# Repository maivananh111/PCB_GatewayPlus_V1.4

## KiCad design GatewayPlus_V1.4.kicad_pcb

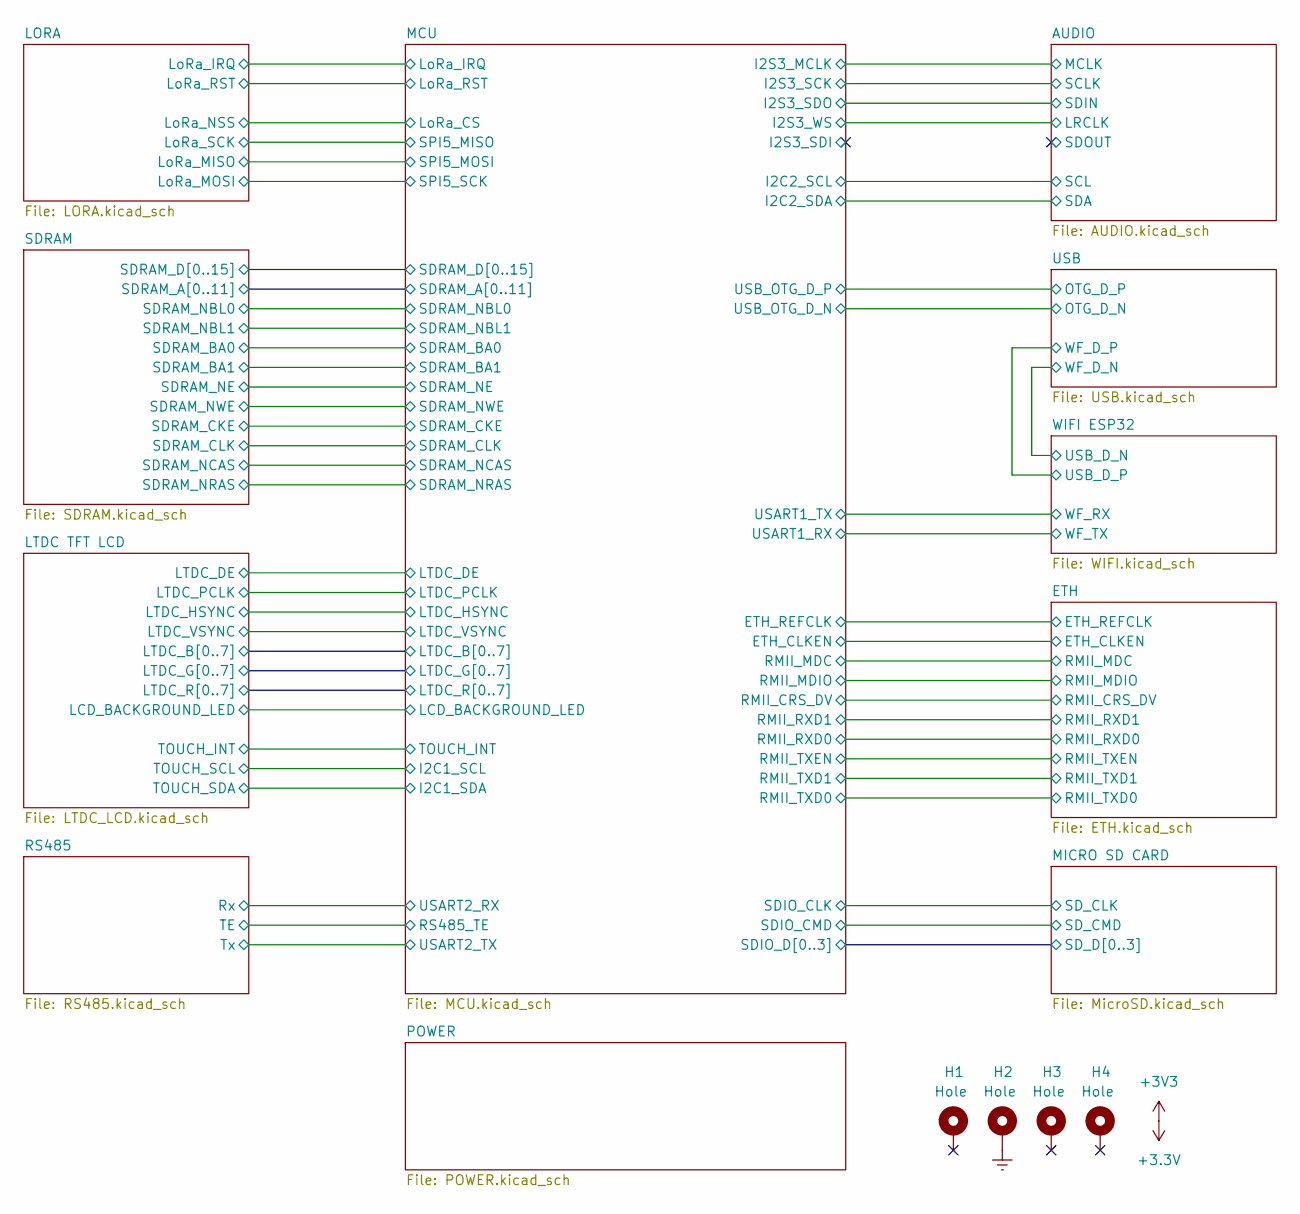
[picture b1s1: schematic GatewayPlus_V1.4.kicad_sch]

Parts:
H1, H2, H3, H4: Hole; MountingHole_3.2mm_M3_Pad_Via

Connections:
Earth: H2.1; also elsewhere on the board

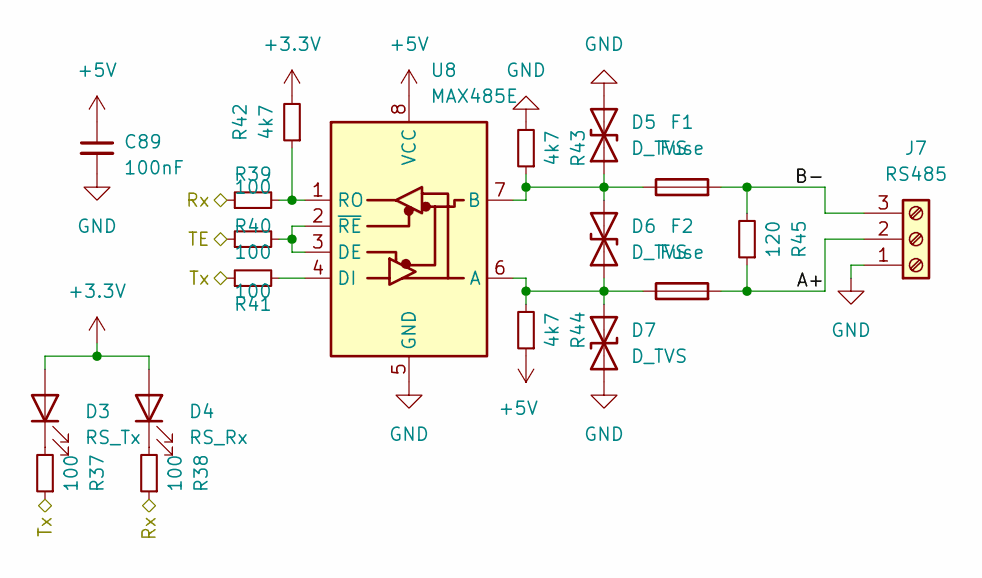
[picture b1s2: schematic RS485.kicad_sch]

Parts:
C89: 100nF; C_0603
D3: RS_Tx; LED_0603
D4: RS_Rx; LED_0603
D5, D6, D7: D_TVS; D_SMA
F1, F2: Fuse; F_1206
J7: RS485; TerminalBlock_Phoenix_MKDS-1,5-3-5.08_1x03_P5.08mm_Horizont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
R37, R38, R39, R40, R41: 100; R_0603
R42, R43, R44: 4k7; R_0603
R45: 120; R_0805
U8: MAX485E; SOIC-8

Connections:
/MCU/RS485_TE: R40.1; also elsewhere on the board
/MCU/USART2_RX: R38.1, R39.1; also elsewhere on the board
/MCU/USART2_TX: R37.1, R41.1; also elsewhere on the board
/RS485/A+: F2.2, J7.2, R45.1
/RS485/B-: F1.2, J7.3, R45.2
GND: C89.2, D5.2 (A2), D7.2 (A2), J7.1, R43.2, U8.5 (GND); also elsewhere on the board
unnamed: D3.1 (K), R37.2
unnamed: D4.1 (K), R38.2
unnamed: D5.1 (A1), D6.2 (A2), F1.1, R43.1, U8.7 (B)
unnamed: D6.1 (A1), D7.1 (A1), F2.1, R44.2, U8.6 (A)
unnamed: R40.2, U8.2 (~RE), U8.3 (DE)
unnamed: R41.2, U8.4 (DI)
unnamed: R39.2, R42.1, U8.1 (RO)

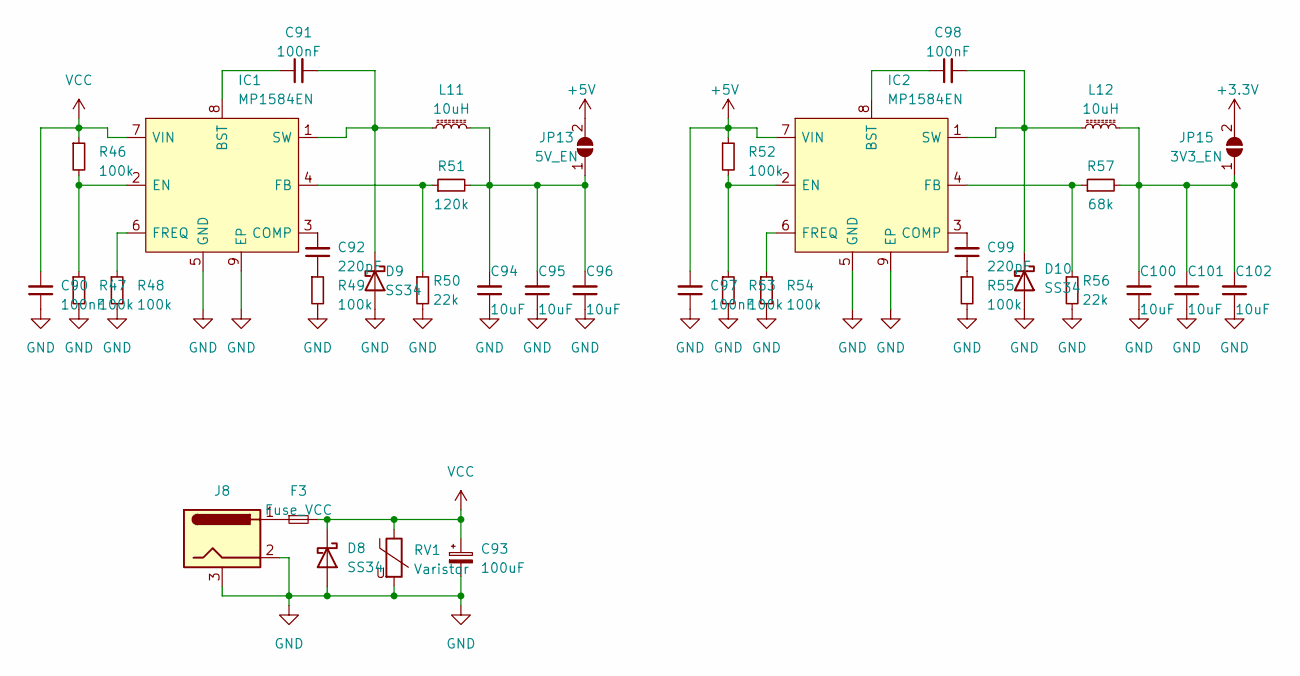
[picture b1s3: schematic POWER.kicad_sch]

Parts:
C90, C91, C97, C98: 100nF; C_0603
C92, C99: 220pF; C_0603
C93: 100uF; CP_Elec_6.3x5.4
C94, C95, C96, C100, C101, C102: 10uF; C_1210
D8, D9, D10: SS34; D_SMA
F3: Fuse_VCC; F_1206
IC1, IC2: MP1584EN; SOIC-8_PAD_VIAS
J8: Conn_Jack-DC; DC_PowerJack_5mm_THT
JP13: 5V_EN; SolderJumper-2_P1.3mm_Open_RoundedPad1.0x1.5mm
JP15: 3V3_EN; SolderJumper-2_P1.3mm_Open_RoundedPad1.0x1.5mm
L11, L12: 10uH; L_Abracon_ASPI-0630LR
R46, R47, R48, R49, R52, R53, R54, R55: 100k; R_0603
R50, R56: 22k; R_0603
R51: 120k; R_0603
R57: 68k; R_0603
RV1: Varistor; RV_Disc_D9mm_W3.3mm_P5mm

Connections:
GND: C90.1, C93.2, C94.1, C95.1, C96.1, C97.1, C100.1, C101.1, C102.1, D8.2 (A), D9.2 (A), D10.2 (A), IC1.5 (GND), IC1.9 (EP), IC2.5 (GND), IC2.9 (EP), J8.2, J8.3, R47.2, R48.2, R49.2, R50.2, R53.2, R54.2, R55.2, R56.2, RV1.2; also elsewhere on the board
unnamed: C92.1, R49.1
unnamed: C99.1, R55.1
unnamed: C91.2, D9.1 (K), IC1.1 (SW), L11.1
unnamed: C98.2, D10.1 (K), IC2.1 (SW), L12.1
unnamed: F3.1, J8.1
unnamed: C91.1, IC1.8 (BST)
unnamed: C92.2, IC1.3 (COMP)
unnamed: IC1.2 (EN), R46.2, R47.1
unnamed: IC1.4 (FB), R50.1, R51.1
unnamed: IC1.6 (FREQ), R48.1
unnamed: C98.1, IC2.8 (BST)
unnamed: C99.2, IC2.3 (COMP)
unnamed: IC2.2 (EN), R52.2, R53.1
unnamed: IC2.4 (FB), R56.1, R57.1
unnamed: IC2.6 (FREQ), R54.1
unnamed: C94.2, C95.2, C96.2, JP13.1 (A), L11.2, R51.2
unnamed: C100.2, C101.2, C102.2, JP15.1 (A), L12.2, R57.2
VCC: C90.2, C93.1, D8.1 (K), F3.2, IC1.7 (VIN), R46.1, RV1.1

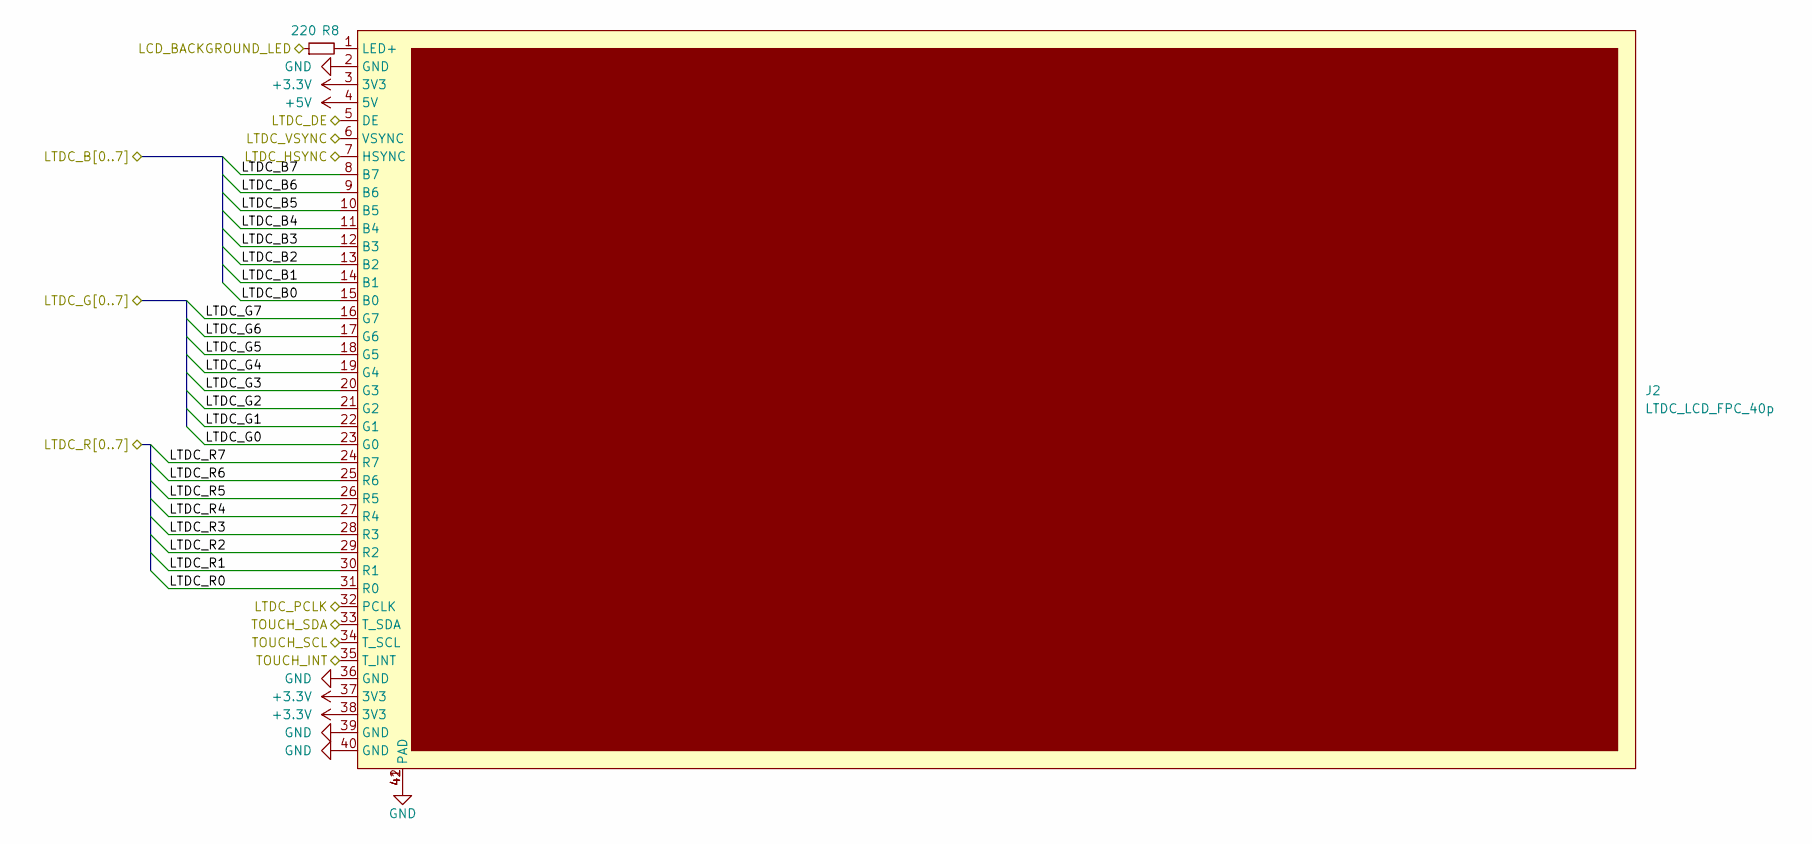
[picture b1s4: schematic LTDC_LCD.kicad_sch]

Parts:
J2: LTDC_LCD_FPC_40p; FPC_40p_Vertical
R8: 220; R_0603

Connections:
/LTDC TFT LCD/LCD_BACKGROUND_LED: R8.1; also elsewhere on the board
/LTDC TFT LCD/LTDC_B0: J2.15 (B0); also elsewhere on the board
/LTDC TFT LCD/LTDC_B1: J2.14 (B1); also elsewhere on the board
/LTDC TFT LCD/LTDC_B2: J2.13 (B2); also elsewhere on the board
/LTDC TFT LCD/LTDC_B3: J2.12 (B3); also elsewhere on the board
/LTDC TFT LCD/LTDC_B4: J2.11 (B4); also elsewhere on the board
/LTDC TFT LCD/LTDC_B5: J2.10 (B5); also elsewhere on the board
/LTDC TFT LCD/LTDC_B6: J2.9 (B6); also elsewhere on the board
/LTDC TFT LCD/LTDC_B7: J2.8 (B7); also elsewhere on the board
/LTDC TFT LCD/LTDC_DE: J2.5 (DE); also elsewhere on the board
/LTDC TFT LCD/LTDC_G0: J2.23 (G0); also elsewhere on the board
/LTDC TFT LCD/LTDC_G1: J2.22 (G1); also elsewhere on the board
/LTDC TFT LCD/LTDC_G2: J2.21 (G2); also elsewhere on the board
/LTDC TFT LCD/LTDC_G3: J2.20 (G3); also elsewhere on the board
/LTDC TFT LCD/LTDC_G4: J2.19 (G4); also elsewhere on the board
/LTDC TFT LCD/LTDC_G5: J2.18 (G5); also elsewhere on the board
/LTDC TFT LCD/LTDC_G6: J2.17 (G6); also elsewhere on the board
/LTDC TFT LCD/LTDC_G7: J2.16 (G7); also elsewhere on the board
/LTDC TFT LCD/LTDC_HSYNC: J2.7 (HSYNC); also elsewhere on the board
/LTDC TFT LCD/LTDC_PCLK: J2.32 (PCLK); also elsewhere on the board
/LTDC TFT LCD/LTDC_R0: J2.31 (R0); also elsewhere on the board
/LTDC TFT LCD/LTDC_R1: J2.30 (R1); also elsewhere on the board
/LTDC TFT LCD/LTDC_R2: J2.29 (R2); also elsewhere on the board
/LTDC TFT LCD/LTDC_R3: J2.28 (R3); also elsewhere on the board
/LTDC TFT LCD/LTDC_R4: J2.27 (R4); also elsewhere on the board
/LTDC TFT LCD/LTDC_R5: J2.26 (R5); also elsewhere on the board
/LTDC TFT LCD/LTDC_R6: J2.25 (R6); also elsewhere on the board
/LTDC TFT LCD/LTDC_R7: J2.24 (R7); also elsewhere on the board
/LTDC TFT LCD/LTDC_VSYNC: J2.6 (VSYNC); also elsewhere on the board
/LTDC TFT LCD/TOUCH_INT: J2.35 (T_INT); also elsewhere on the board
/LTDC TFT LCD/TOUCH_SCL: J2.34 (T_SCL); also elsewhere on the board
/LTDC TFT LCD/TOUCH_SDA: J2.33 (T_SDA); also elsewhere on the board
GND: J2.2 (GND), J2.36 (GND), J2.39 (GND), J2.40 (GND), J2.41 (PAD), J2.42 (PAD); also elsewhere on the board
unnamed: J2.1 (LED+), R8.2

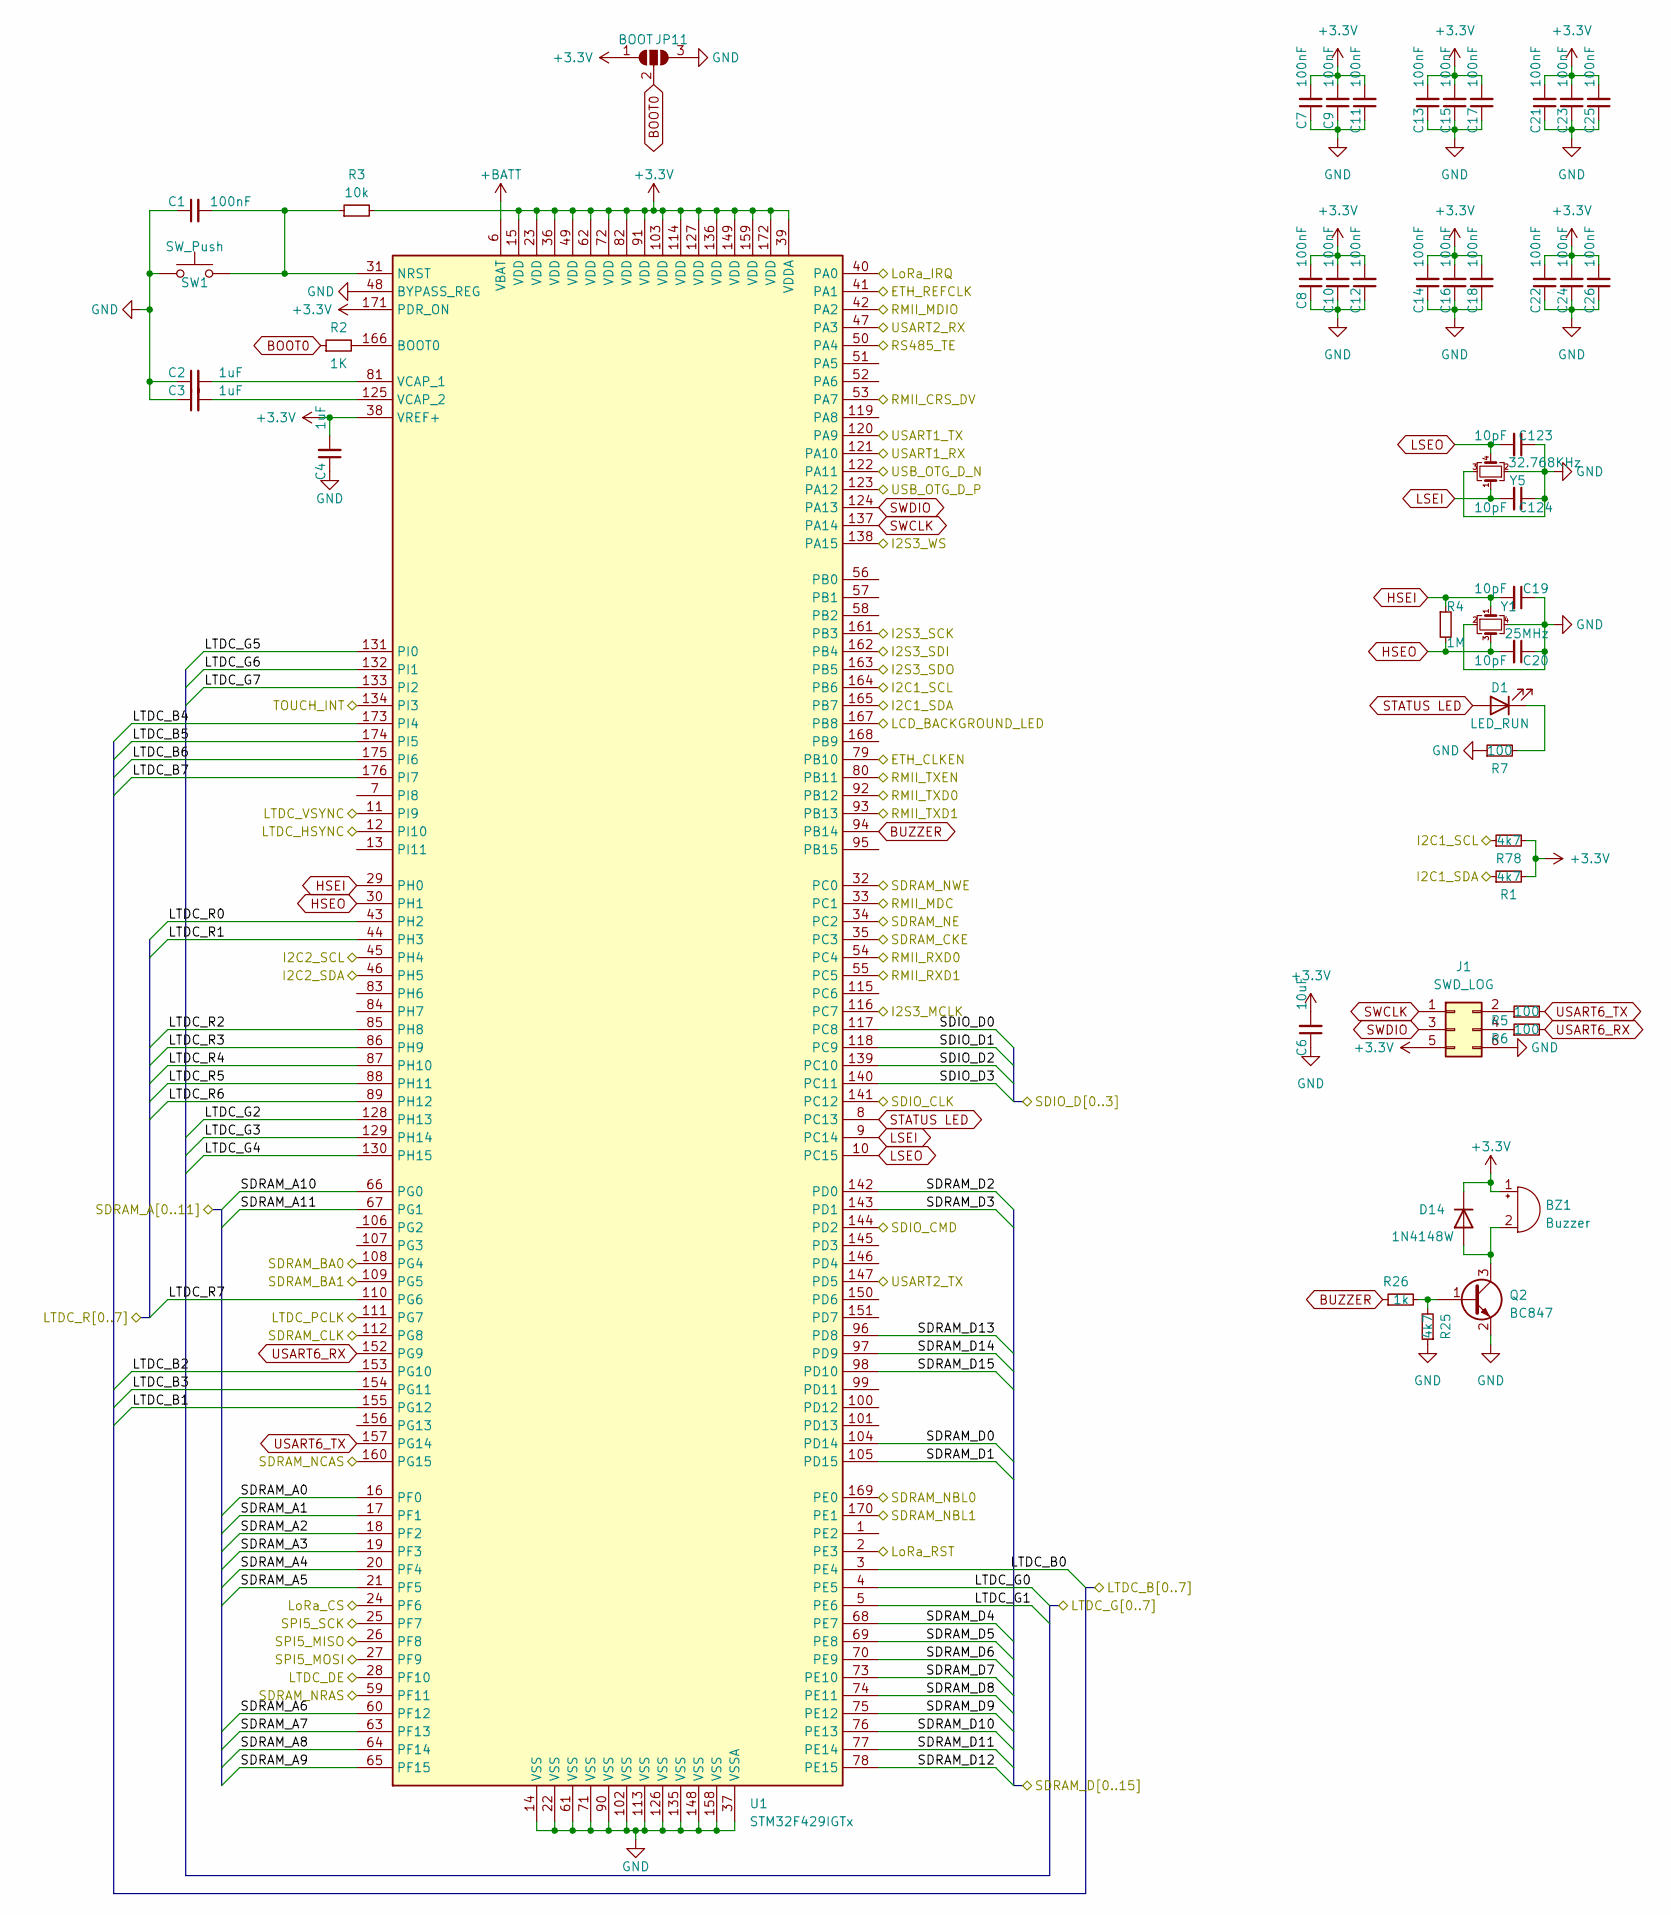
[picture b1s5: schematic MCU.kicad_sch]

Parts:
BZ1: Buzzer; MagneticBuzzer_ProSignal_ABT-410-RC
C1, C7, C8, C9, C10, C11, C12, C13, C14, C15, C16, C17, C18, C21, C22, C23, C24, C25, C26: 100nF; C_0603
C2, C3, C4: 1uF; C_0603
C6: 10uF; C_1206
C19, C20, C123, C124: 10pF; C_0603
D1: LED_RUN; LED_0603
D14: 1N4148W; D_SOD-123F
J1: SWD_LOG; PinHeader_2x03_P2.54mm_Horizontal
JP11: BOOT; Jump3_0603_Open
Q2: BC847; SOT23-3
R1, R25, R78: 4k7; R_0603
R2: 1K; R_0603
R3: 10k; R_0603
R4: 1M; R_0603
R5, R6, R7: 100; R_0603
R26: 1k; R_0603
SW1: SW_Push; SW_SPST_CK_RS282G05A3
U1: STM32F429IGTx; LQFP-176_24x24
Y1: 25MHz; Crystal_SMD_3225-4Pin_3.2x2.5mm
Y5: 32.768KHz; MC306327680KE3ROHS

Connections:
+BATT: U1.6 (VBAT)
/AUDIO/LRCLK: U1.138 (PA15); also elsewhere on the board
/AUDIO/MCLK: U1.116 (PC7); also elsewhere on the board
/AUDIO/SCL: U1.45 (PH4); also elsewhere on the board
/AUDIO/SCLK: U1.161 (PB3); also elsewhere on the board
/AUDIO/SDA: U1.46 (PH5); also elsewhere on the board
/AUDIO/SDIN: U1.163 (PB5); also elsewhere on the board
/ETH/ETH_REFCLK: U1.41 (PA1); also elsewhere on the board
/ETH/RMII_CRS_DV: U1.53 (PA7); also elsewhere on the board
/ETH/RMII_MDC: U1.33 (PC1); also elsewhere on the board
/ETH/RMII_MDIO: U1.42 (PA2); also elsewhere on the board
/ETH/RMII_RXD0: U1.54 (PC4); also elsewhere on the board
/ETH/RMII_RXD1: U1.55 (PC5); also elsewhere on the board
/ETH/RMII_TXD0: U1.92 (PB12); also elsewhere on the board
/ETH/RMII_TXD1: U1.93 (PB13); also elsewhere on the board
/ETH/RMII_TXEN: U1.80 (PB11); also elsewhere on the board
/LORA/LoRa_IRQ: U1.40 (PA0); also elsewhere on the board
/LORA/LoRa_MISO: U1.27 (PF9); also elsewhere on the board
/LORA/LoRa_MOSI: U1.25 (PF7); also elsewhere on the board
/LORA/LoRa_NSS: U1.24 (PF6); also elsewhere on the board
/LORA/LoRa_RST: U1.2 (PE3); also elsewhere on the board
/LORA/LoRa_SCK: U1.26 (PF8); also elsewhere on the board
/LTDC TFT LCD/LCD_BACKGROUND_LED: U1.167 (PB8); also elsewhere on the board
/LTDC TFT LCD/LTDC_B0: U1.3 (PE4); also elsewhere on the board
/LTDC TFT LCD/LTDC_B1: U1.155 (PG12); also elsewhere on the board
/LTDC TFT LCD/LTDC_B2: U1.153 (PG10); also elsewhere on the board
/LTDC TFT LCD/LTDC_B3: U1.154 (PG11); also elsewhere on the board
/LTDC TFT LCD/LTDC_B4: U1.173 (PI4); also elsewhere on the board
/LTDC TFT LCD/LTDC_B5: U1.174 (PI5); also elsewhere on the board
/LTDC TFT LCD/LTDC_B6: U1.175 (PI6); also elsewhere on the board
/LTDC TFT LCD/LTDC_B7: U1.176 (PI7); also elsewhere on the board
/LTDC TFT LCD/LTDC_DE: U1.28 (PF10); also elsewhere on the board
/LTDC TFT LCD/LTDC_G0: U1.4 (PE5); also elsewhere on the board
/LTDC TFT LCD/LTDC_G1: U1.5 (PE6); also elsewhere on the board
/LTDC TFT LCD/LTDC_G2: U1.128 (PH13); also elsewhere on the board
/LTDC TFT LCD/LTDC_G3: U1.129 (PH14); also elsewhere on the board
/LTDC TFT LCD/LTDC_G4: U1.130 (PH15); also elsewhere on the board
/LTDC TFT LCD/LTDC_G5: U1.131 (PI0); also elsewhere on the board
/LTDC TFT LCD/LTDC_G6: U1.132 (PI1); also elsewhere on the board
/LTDC TFT LCD/LTDC_G7: U1.133 (PI2); also elsewhere on the board
/LTDC TFT LCD/LTDC_HSYNC: U1.12 (PI10); also elsewhere on the board
/LTDC TFT LCD/LTDC_PCLK: U1.111 (PG7); also elsewhere on the board
/LTDC TFT LCD/LTDC_R0: U1.43 (PH2); also elsewhere on the board
/LTDC TFT LCD/LTDC_R1: U1.44 (PH3); also elsewhere on the board
/LTDC TFT LCD/LTDC_R2: U1.85 (PH8); also elsewhere on the board
/LTDC TFT LCD/LTDC_R3: U1.86 (PH9); also elsewhere on the board
/LTDC TFT LCD/LTDC_R4: U1.87 (PH10); also elsewhere on the board
/LTDC TFT LCD/LTDC_R5: U1.88 (PH11); also elsewhere on the board
/LTDC TFT LCD/LTDC_R6: U1.89 (PH12); also elsewhere on the board
/LTDC TFT LCD/LTDC_R7: U1.110 (PG6); also elsewhere on the board
/LTDC TFT LCD/LTDC_VSYNC: U1.11 (PI9); also elsewhere on the board
/LTDC TFT LCD/TOUCH_INT: U1.134 (PI3); also elsewhere on the board
/LTDC TFT LCD/TOUCH_SCL: R78.1, U1.164 (PB6); also elsewhere on the board
/LTDC TFT LCD/TOUCH_SDA: R1.1, U1.165 (PB7); also elsewhere on the board
/MCU/ETH_CLKEN: U1.79 (PB10)
/MCU/I2S3_SDI: U1.162 (PB4)
/MCU/RS485_TE: U1.50 (PA4); also elsewhere on the board
/MCU/SDIO_CLK: U1.141 (PC12); also elsewhere on the board
/MCU/SDIO_CMD: U1.144 (PD2); also elsewhere on the board
/MCU/SDIO_D0: U1.117 (PC8); also elsewhere on the board
/MCU/SDIO_D1: U1.118 (PC9); also elsewhere on the board
/MCU/SDIO_D2: U1.139 (PC10); also elsewhere on the board
/MCU/SDIO_D3: U1.140 (PC11); also elsewhere on the board
/MCU/SDRAM_A0: U1.16 (PF0); also elsewhere on the board
/MCU/SDRAM_A1: U1.17 (PF1); also elsewhere on the board
/MCU/SDRAM_A2: U1.18 (PF2); also elsewhere on the board
/MCU/SDRAM_A3: U1.19 (PF3); also elsewhere on the board
/MCU/SDRAM_A4: U1.20 (PF4); also elsewhere on the board
/MCU/SDRAM_A5: U1.21 (PF5); also elsewhere on the board
/MCU/SDRAM_A6: U1.60 (PF12); also elsewhere on the board
/MCU/SDRAM_A7: U1.63 (PF13); also elsewhere on the board
/MCU/SDRAM_A8: U1.64 (PF14); also elsewhere on the board
/MCU/SDRAM_A9: U1.65 (PF15); also elsewhere on the board
/MCU/SDRAM_A10: U1.66 (PG0); also elsewhere on the board
/MCU/SDRAM_A11: U1.67 (PG1); also elsewhere on the board
/MCU/SDRAM_BA0: U1.108 (PG4); also elsewhere on the board
/MCU/SDRAM_BA1: U1.109 (PG5); also elsewhere on the board
/MCU/SDRAM_CKE: U1.35 (PC3); also elsewhere on the board
/MCU/SDRAM_CLK: U1.112 (PG8); also elsewhere on the board
/MCU/SDRAM_D0: U1.104 (PD14); also elsewhere on the board
/MCU/SDRAM_D1: U1.105 (PD15); also elsewhere on the board
/MCU/SDRAM_D2: U1.142 (PD0); also elsewhere on the board
/MCU/SDRAM_D3: U1.143 (PD1); also elsewhere on the board
/MCU/SDRAM_D4: U1.68 (PE7); also elsewhere on the board
/MCU/SDRAM_D5: U1.69 (PE8); also elsewhere on the board
/MCU/SDRAM_D6: U1.70 (PE9); also elsewhere on the board
/MCU/SDRAM_D7: U1.73 (PE10); also elsewhere on the board
/MCU/SDRAM_D8: U1.74 (PE11); also elsewhere on the board
/MCU/SDRAM_D9: U1.75 (PE12); also elsewhere on the board
/MCU/SDRAM_D10: U1.76 (PE13); also elsewhere on the board
/MCU/SDRAM_D11: U1.77 (PE14); also elsewhere on the board
/MCU/SDRAM_D12: U1.78 (PE15); also elsewhere on the board
/MCU/SDRAM_D13: U1.96 (PD8); also elsewhere on the board
/MCU/SDRAM_D14: U1.97 (PD9); also elsewhere on the board
/MCU/SDRAM_D15: U1.98 (PD10); also elsewhere on the board
/MCU/SDRAM_NBL0: U1.169 (PE0); also elsewhere on the board
/MCU/SDRAM_NBL1: U1.170 (PE1); also elsewhere on the board
/MCU/SDRAM_NCAS: U1.160 (PG15); also elsewhere on the board
/MCU/SDRAM_NE: U1.34 (PC2); also elsewhere on the board
/MCU/SDRAM_NRAS: U1.59 (PF11); also elsewhere on the board
/MCU/SDRAM_NWE: U1.32 (PC0); also elsewhere on the board
/MCU/USART1_RX: U1.121 (PA10); also elsewhere on the board
/MCU/USART1_TX: U1.120 (PA9); also elsewhere on the board
/MCU/USART2_RX: U1.47 (PA3); also elsewhere on the board
/MCU/USART2_TX: U1.147 (PD5); also elsewhere on the board
/MCU/USB_OTG_D_N: U1.122 (PA11); also elsewhere on the board
/MCU/USB_OTG_D_P: U1.123 (PA12); also elsewhere on the board
BOOT0: JP11.2 (C), R2.1
BUZZER: R26.1, U1.94 (PB14)
GND: C1.1, C2.1, C3.1, C4.1, C6.1, C7.1, C8.1, C9.1, C10.1, C11.1, C12.1, C13.1, C14.1, C15.1, C16.1, C17.1, C18.1, C19.1, C20.1, C21.1, C22.1, C23.1, C24.1, C25.1, C26.1, C123.1, C124.1, J1.6, JP11.3 (B), Q2.2 (E), R7.1, R25.1, SW1.1, U1.14 (VSS), U1.22 (VSS), U1.37 (VSSA), U1.48 (BYPASS_REG), U1.61 (VSS), U1.71 (VSS), U1.90 (VSS), U1.102 (VSS), U1.113 (VSS), U1.126 (VSS), U1.135 (VSS), U1.148 (VSS), U1.158 (VSS), Y1.2, Y1.4, Y5.2, Y5.3; also elsewhere on the board
HSEI: C19.2, R4.1, U1.29 (PH0), Y1.1
HSEO: C20.2, R4.2, U1.30 (PH1), Y1.3
LSEI: C124.2, U1.9 (PC14), Y5.1
LSEO: C123.2, U1.10 (PC15), Y5.4
unnamed: BZ1.2 (+), D14.2 (A), Q2.3 (C)
unnamed: D1.1 (K), R7.2
unnamed: J1.2, R5.1
unnamed: J1.4, R6.1
unnamed: Q2.1 (B), R25.2, R26.2
unnamed: R2.2, U1.166 (BOOT0)
unnamed: C1.2, R3.1, SW1.2, U1.31 (NRST)
unnamed: C2.2, U1.81 (VCAP_1)
unnamed: C3.2, U1.125 (VCAP_2)
STATUS LED: D1.2 (A), U1.8 (PC13)
SWCLK: J1.1, U1.137 (PA14)
SWDIO: J1.3, U1.124 (PA13)
USART6_RX: R6.2, U1.152 (PG9)
USART6_TX: R5.2, U1.157 (PG14)

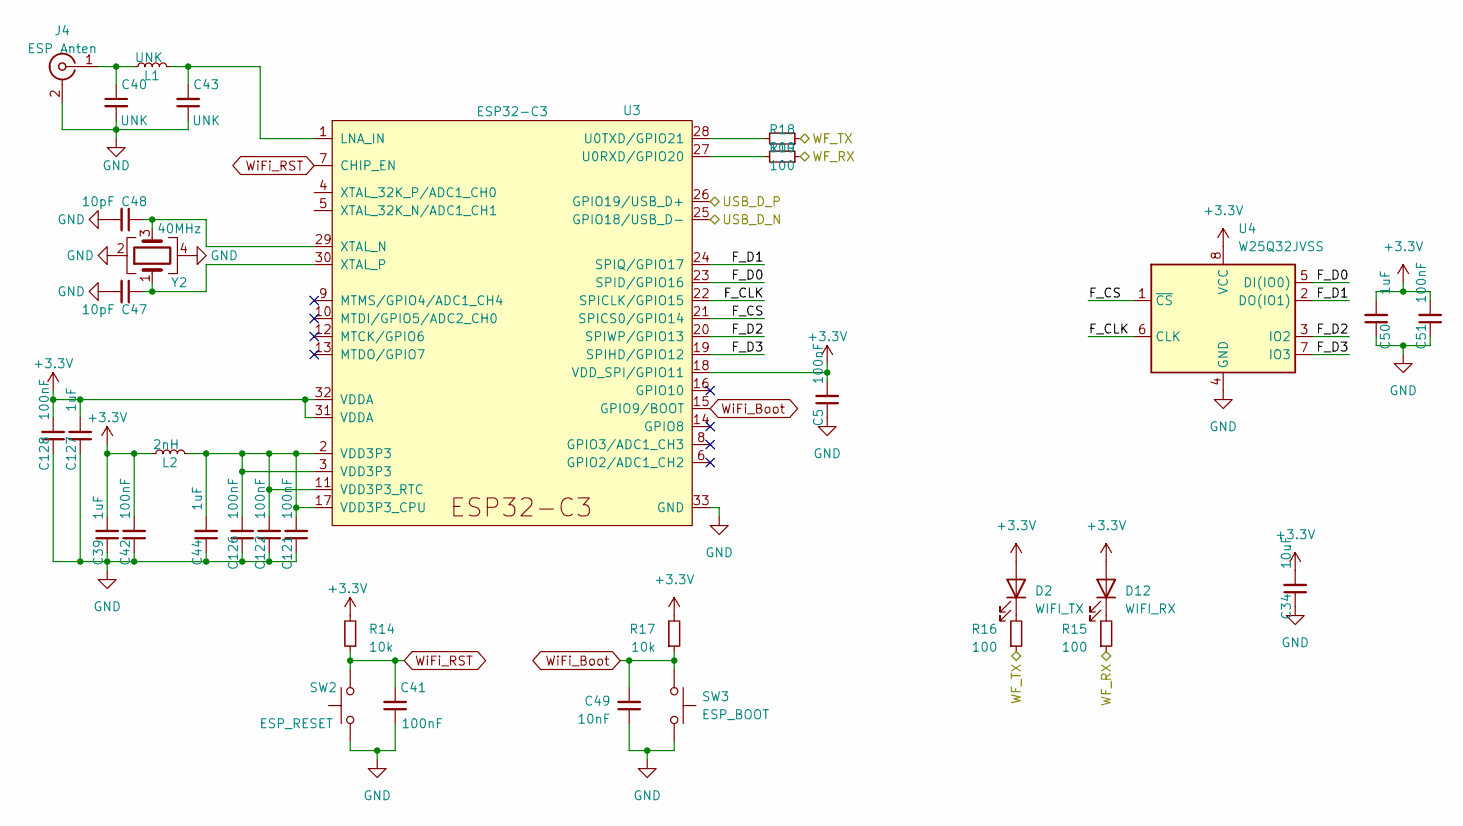
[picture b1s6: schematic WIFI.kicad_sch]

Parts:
C5, C41, C42, C51, C121, C122, C126, C128: 100nF; C_0603
C34: 10uF; C_1206
C39, C44, C50, C127: 1uF; C_0603
C40, C43: UNK; C_0603
C47, C48: 10pF; C_0603
C49: 10nF; C_0603
D2: WIFI_TX; LED_0603
D12: WIFI_RX; LED_0603
J4: ESP Anten; IPEX_Antena_Connector
L1: UNK; L_0603
L2: 2nH; L_0603
R14, R17: 10k; R_0603
R15, R16, R18, R19: 100; R_0603
SW2: ESP_RESET; SW_SPST_CK_RS282G05A3
SW3: ESP_BOOT; SW_SPST_CK_RS282G05A3
U3: ESP32-C3; QFN-32_5x5_PAD-VIAS
U4: W25Q32JVSS; SOIC-8_5.23x5.23
Y2: 40MHz; Crystal_SMD_3225-4Pin_3.2x2.5mm

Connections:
/MCU/USART1_RX: R16.1, R18.1; also elsewhere on the board
/MCU/USART1_TX: R15.1, R19.1; also elsewhere on the board
/USB/WF_D_N: U3.25 (GPIO18/USB_D-); also elsewhere on the board
/USB/WF_D_P: U3.26 (GPIO19/USB_D+); also elsewhere on the board
/WIFI ESP32/F_CLK: U3.22 (SPICLK/GPIO15), U4.6 (CLK)
/WIFI ESP32/F_CS: U3.21 (SPICS0/GPIO14), U4.1 (~CS)
/WIFI ESP32/F_D0: U3.23 (SPID/GPIO16), U4.5 (DI(IO0))
/WIFI ESP32/F_D1: U3.24 (SPIQ/GPIO17), U4.2 (DO(IO1))
/WIFI ESP32/F_D2: U3.20 (SPIWP/GPIO13), U4.3 (IO2)
/WIFI ESP32/F_D3: U3.19 (SPIHD/GPIO12), U4.7 (IO3)
GND: C5.1, C34.1, C39.1, C40.2, C41.1, C42.1, C43.1, C44.1, C47.2, C48.2, C49.1, C50.1, C51.1, C121.1, C122.1, C126.1, C127.1, C128.1, J4.2 (Ext), SW2.1, SW3.1, U3.33 (GND), U4.4 (GND), Y2.2, Y2.4; also elsewhere on the board
unnamed: D2.1 (K), R16.2
unnamed: D12.1 (K), R15.2
unnamed: C40.1, J4.1 (In), L1.1
unnamed: C43.2, L1.2, U3.1 (LNA_IN)
unnamed: R19.2, U3.27 (U0RXD/GPIO20)
unnamed: R18.2, U3.28 (U0TXD/GPIO21)
unnamed: C44.2, C121.2, C122.2, C126.2, L2.2, U3.2 (VDD3P3), U3.3 (VDD3P3), U3.11 (VDD3P3_RTC), U3.17 (VDD3P3_CPU)
unnamed: C48.1, U3.29 (XTAL_N), Y2.3
unnamed: C47.1, U3.30 (XTAL_P), Y2.1
WiFi_Boot: C49.2, R17.1, SW3.2, U3.15 (GPIO9/BOOT)
WiFi_RST: C41.2, R14.1, SW2.2, U3.7 (CHIP_EN)

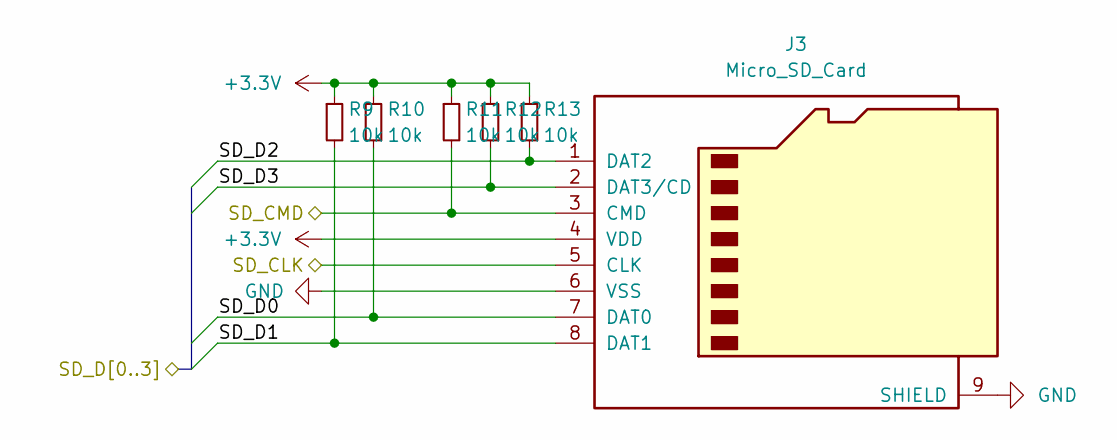
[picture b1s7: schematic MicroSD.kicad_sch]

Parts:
J3: Micro_SD_Card; MicroSD_Socket
R9, R10, R11, R12, R13: 10k; R_0603

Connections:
/MCU/SDIO_CLK: J3.5 (CLK); also elsewhere on the board
/MCU/SDIO_CMD: J3.3 (CMD), R11.2; also elsewhere on the board
/MCU/SDIO_D0: J3.7 (DAT0), R10.2; also elsewhere on the board
/MCU/SDIO_D1: J3.8 (DAT1), R9.2; also elsewhere on the board
/MCU/SDIO_D2: J3.1 (DAT2), R13.2; also elsewhere on the board
/MCU/SDIO_D3: J3.2 (DAT3/CD), R12.2; also elsewhere on the board
GND: J3.6 (VSS), J3.9 (SHIELD); also elsewhere on the board

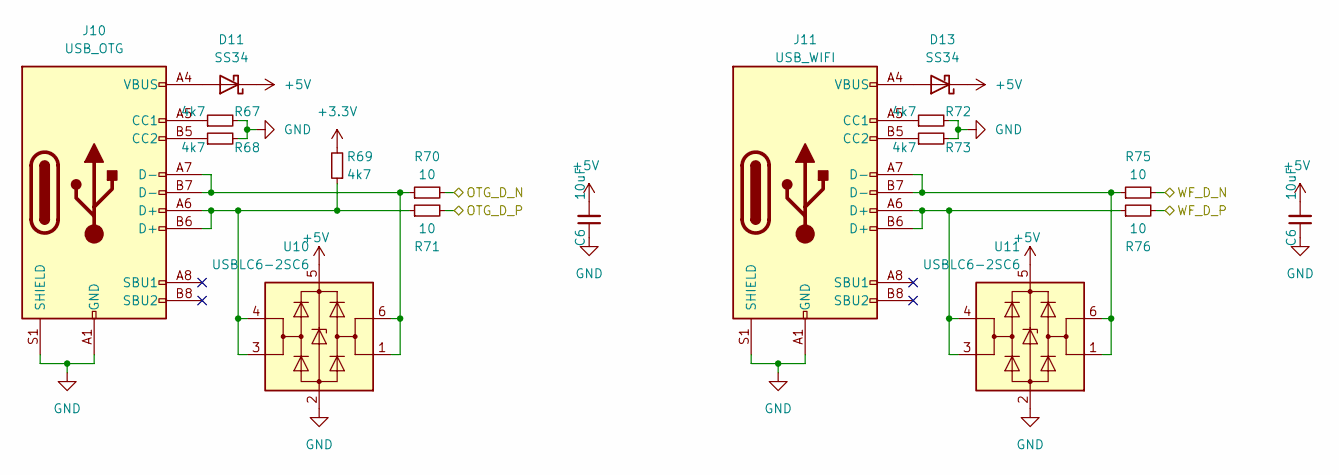
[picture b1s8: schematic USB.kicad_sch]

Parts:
C6: 10uF; C_1206
D11, D13: SS34; D_SMA
J10: USB_OTG; USB-C_SMD_1
J11: USB_WIFI; USB-C_SMD_1
R67, R68, R69, R72, R73: 4k7; R_0603
R70, R71, R75, R76: 10; R_0603
U10, U11: USBLC6-2SC6; SOT23-6

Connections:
/MCU/USB_OTG_D_N: R70.2; also elsewhere on the board
/MCU/USB_OTG_D_P: R71.2; also elsewhere on the board
/USB/WF_D_N: R75.2; also elsewhere on the board
/USB/WF_D_P: R76.2; also elsewhere on the board
GND: C6.1, J10.A1 (GND), J10.A12 (GND), J10.B1 (GND), J10.B12 (GND), J10.S1 (SHIELD), J11.A1 (GND), J11.A12 (GND), J11.B1 (GND), J11.B12 (GND), J11.S1 (SHIELD), R67.2, R68.2, R72.2, R73.2, U10.2 (GND), U11.2 (GND); also elsewhere on the board
unnamed: D11.2 (A), J10.A4 (VBUS), J10.A9 (VBUS), J10.B4 (VBUS), J10.B9 (VBUS)
unnamed: D13.2 (A), J11.A4 (VBUS), J11.A9 (VBUS), J11.B4 (VBUS), J11.B9 (VBUS)
unnamed: J10.A5 (CC1), R67.1
unnamed: J10.B5 (CC2), R68.1
unnamed: J10.A6 (D+), J10.B6 (D+), R69.1, R71.1, U10.3 (I/O2), U10.4 (I/O2)
unnamed: J10.A7 (D-), J10.B7 (D-), R70.1, U10.1 (I/O1), U10.6 (I/O1)
unnamed: J11.A5 (CC1), R72.1
unnamed: J11.B5 (CC2), R73.1
unnamed: J11.A6 (D+), J11.B6 (D+), R76.1, U11.3 (I/O2), U11.4 (I/O2)
unnamed: J11.A7 (D-), J11.B7 (D-), R75.1, U11.1 (I/O1), U11.6 (I/O1)

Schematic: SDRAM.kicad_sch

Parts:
C27, C30: 1uF; C_0603
C28, C29, C31, C32, C33: 100nF; C_0603
U2: IS42S16400J - HY57V641620E; TSOP-II-54_22.2x10.16

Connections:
/MCU/SDRAM_A0: U2.23 (A0); also elsewhere on the board
/MCU/SDRAM_A1: U2.24 (A1); also elsewhere on the board
/MCU/SDRAM_A2: U2.25 (A2); also elsewhere on the board
/MCU/SDRAM_A3: U2.26 (A3); also elsewhere on the board
/MCU/SDRAM_A4: U2.29 (A4); also elsewhere on the board
/MCU/SDRAM_A5: U2.30 (A5); also elsewhere on the board
/MCU/SDRAM_A6: U2.31 (A6); also elsewhere on the board
/MCU/SDRAM_A7: U2.32 (A7); also elsewhere on the board
/MCU/SDRAM_A8: U2.33 (A8); also elsewhere on the board
/MCU/SDRAM_A9: U2.34 (A9); also elsewhere on the board
/MCU/SDRAM_A10: U2.22 (A10); also elsewhere on the board
/MCU/SDRAM_A11: U2.35 (A11); also elsewhere on the board
/MCU/SDRAM_BA0: U2.20 (BA0); also elsewhere on the board
/MCU/SDRAM_BA1: U2.21 (BA1); also elsewhere on the board
/MCU/SDRAM_CKE: U2.37 (CKE); also elsewhere on the board
/MCU/SDRAM_CLK: U2.38 (CLK); also elsewhere on the board
/MCU/SDRAM_D0: U2.2 (DQ0); also elsewhere on the board
/MCU/SDRAM_D1: U2.4 (DQ1); also elsewhere on the board
/MCU/SDRAM_D2: U2.5 (DQ2); also elsewhere on the board
/MCU/SDRAM_D3: U2.7 (DQ3); also elsewhere on the board
/MCU/SDRAM_D4: U2.8 (DQ4); also elsewhere on the board
/MCU/SDRAM_D5: U2.10 (DQ5); also elsewhere on the board
/MCU/SDRAM_D6: U2.11 (DQ6); also elsewhere on the board
/MCU/SDRAM_D7: U2.13 (DQ7); also elsewhere on the board
/MCU/SDRAM_D8: U2.42 (DQ8); also elsewhere on the board
/MCU/SDRAM_D9: U2.44 (DQ9); also elsewhere on the board
/MCU/SDRAM_D10: U2.45 (DQ10); also elsewhere on the board
/MCU/SDRAM_D11: U2.47 (DQ11); also elsewhere on the board
/MCU/SDRAM_D12: U2.48 (DQ12); also elsewhere on the board
/MCU/SDRAM_D13: U2.50 (DQ13); also elsewhere on the board
/MCU/SDRAM_D14: U2.51 (DQ14); also elsewhere on the board
/MCU/SDRAM_D15: U2.53 (DQ15); also elsewhere on the board
/MCU/SDRAM_NBL0: U2.15 (LDQM); also elsewhere on the board
/MCU/SDRAM_NBL1: U2.39 (UDQM); also elsewhere on the board
/MCU/SDRAM_NCAS: U2.17 (~CAS); also elsewhere on the board
/MCU/SDRAM_NE: U2.19 (~CS); also elsewhere on the board
/MCU/SDRAM_NRAS: U2.18 (~RAS); also elsewhere on the board
/MCU/SDRAM_NWE: U2.16 (~WE); also elsewhere on the board
GND: C27.1, C28.1, C29.1, C30.1, C31.1, C32.1, C33.1, U2.6 (GNDQ), U2.12 (GNDQ), U2.28 (GND), U2.41 (GND), U2.46 (GNDQ), U2.52 (GNDQ), U2.54 (GND); also elsewhere on the board

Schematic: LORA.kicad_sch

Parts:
C53: 1uF; C_0603
C54, C55: 10pF; C_0603
C56, C57, C58, C61, C62: 100nF; C_0603
C63, C64, C65, C66, C67, C68, C69, C70, C71, C72, C73, C74, C75, C76, C77, C78: C_Small; C_0603
J5: LoRa_Anten; IPEX_Antena_Connector
L3, L4, L5, L6, L7, L8, L9: L_Small; L_0603
Q1: BC847; SOT23-3
R20, R21, R22: R_Small; R_0603
U5: SX1278; QFN-28_6x6_PAD
U6: MASWSS0192; SOT-363_SC-70-6
Y3: 32MHz; Crystal_SMD_3225-4Pin_3.2x2.5mm

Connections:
/LORA/LoRa_IRQ: U5.8 (DIO0); also elsewhere on the board
/LORA/LoRa_MISO: U5.17 (MISO); also elsewhere on the board
/LORA/LoRa_MOSI: U5.18 (MOSI); also elsewhere on the board
/LORA/LoRa_NSS: U5.19 (NSS); also elsewhere on the board
/LORA/LoRa_RST: U5.7 (~RESET); also elsewhere on the board
/LORA/LoRa_SCK: U5.16 (SCK); also elsewhere on the board
GND: C53.2, C54.1, C55.1, C56.2, C57.2, C58.2, C61.2, C62.2, C63.2, C64.2, C66.2, C68.2, C70.1, C72.1, C74.1, C75.1, C76.1, C77.1, C78.1, J5.2 (Ext), L3.2, Q1.2 (E), U5.15 (GND), U5.21 (GND), U5.22 (GND), U5.23 (GND), U5.26 (GND), U5.29 (GND), U6.2 (GND), Y3.2, Y3.4; also elsewhere on the board
unnamed: C65.1, L4.2
unnamed: C65.2, C67.1
unnamed: C68.1, C69.1, L5.2, L6.1
unnamed: C69.2, C70.2, C71.1, L7.1
unnamed: C71.2, C72.2, C73.1, L7.2, L8.1
unnamed: C78.2, J5.1 (In), L9.2
unnamed: Q1.1 (B), R21.2
unnamed: C75.2, Q1.3 (C), R22.1, U6.4 (V2)
unnamed: L5.1, U5.27 (PA_BOOST)
unnamed: L3.1, L4.1, U5.1 (RFI_LF)
unnamed: R20.1, R21.1, U5.20 (RXTX/RF_MOD)
unnamed: C62.1, U5.2 (VR_ANA)
unnamed: C61.1, U5.4 (VR_DIG)
unnamed: C63.1, C64.1, C66.1, L6.2, U5.25 (VR_PA)
unnamed: C54.2, U5.5 (XTA), Y3.3
unnamed: C55.2, U5.6 (XTB), Y3.1
unnamed: C67.2, U6.1 (RF1)
unnamed: C73.2, C74.2, L8.2, U6.3 (RF2)
unnamed: C77.2, L9.1, U6.5 (RFC)
unnamed: C76.2, R20.2, U6.6 (V1)
